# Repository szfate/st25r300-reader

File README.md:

# ST25R300-reader — NFC Reader Board

A compact, high-power NFC reader module built around the STMicroelectronics ST25R300 series. Packed into a 40x40mm board, it drives an onboard 4-turn center-tapped PCB antenna at up to 2.2 W, giving 4+ cm read range across a wide variety of tag form factors — including hard-to-read rings.

## Features

- NFC-A/B (ISO14443A/B), NFC-F (FeliCa), NFC-V (ISO15693, up to 212 kbps) support
- NFC initiator, target, reader, and card emulation modes; EMVCo PCD 3.2a compliant analog/digital
- Low-power card detection (LPCD) via I/Q antenna signal measurement
- Up to 2.2 W RF output power (extended range capable)
- 4+ cm read range across various tag form factors, including rings
- Dual supply: 5 V antenna/RF rail, separate IO supply
- Compact 40x40mm board

## The ST25R300 Chip

The ST25R300 is STMicroelectronics' high-performance NFC universal reader/transceiver IC. It supports NFC-A/B (ISO14443A/B), NFC-F (FeliCa), and NFC-V (ISO15693) protocols, and can operate as an NFC initiator, target, reader, or card emulator. It is designed to be compliant with the EMVCo PCD 3.2a analog and digital standards, making it suitable for contactless payment reader designs as well as general NFC/RFID applications.

- Manufacturer: STMicroelectronics
- Part: ST25R300-AQET
- Package: 32-pin UFQFPN-EP
- Datasheet/product page: https://www.st.com/en/nfc/st25r300.html
- Host interface: SPI
- Operating frequency: 13.56 MHz carrier (max 27.12 MHz internal)
- Supply range: wide supply voltage range 2.7 to 6.0 V (VDD); wide peripheral communication supply range 1.65 to 5.5 V (IO)
- Operating temperature: -40°C to +105°C
- RF output power: up to 2.2 W (extended range)
- Key features: low-power card detection (LPCD) using I/Q antenna signal measurement; NFC-A/NFC-F card emulation

## Board Specifications

| Spec | Value |
|---|---|
| Supply voltage | Dual rail: VTX 5 V antenna/RF supply; VIO host-provided IO supply (1.65–5.5 V) |
| Read range | 4+ cm, tested across various tag form factors including rings |
| Antenna tuning | Tuned to 15 Ω |
| Current consumption | ~0.25 A @ 5V|
| Operating temperature | -40°C to +105°C (chip rating — confirm board components match) |
| Dimensions | 40 x 40 mm |
| Antenna | Onboard PCB trace antenna, 4 turns, center-tapped |
| Host interface | SPI |

## Pinout

Connector: Molex PicoBlade 53261-0971, 1x9, 1.25mm pitch (`Conn_01x09`)

| Pin | Signal | Type | Description |
|---|---|---|---|
| 1 | CS | Input | SPI chip select (active low) |
| 2 | MOSI | Input | SPI master out / slave in |
| 3 | SCLK | Input | SPI clock |
| 4 | MISO | Output | SPI master in / slave out |
| 5 | RST | Input | Reset (optional — pulled down on-board; drive high to release reset) |
| 6 | IRQ | Output | Interrupt output |
| 7 | VTX | Power | Antenna/RF supply (5 V) |
| 8 | VIO | Power | IO supply (host-provided, 1.65–5.5 V) |
| 9 | GND | Power | Ground |

Signal directions in the table above are from the module's perspective: host → board for inputs, board → host for outputs.

## Connector

On-board connector: Molex PicoBlade, 1.25mm pitch, 1x9 position (53261-0971).

## Mechanical

| Spec | Value |
|---|---|
| Board dimensions | 40 x 40 mm |
| Mounting holes | 4x M3 (3.2 mm drill) on a 25 x 25 mm grid |
| Board thickness | 1.2 mm |
| Layer count | 4 |

Any metal near the antenna will detune the frequency and reduce read range/performance. Keep the antenna area clear of screws, connectors, enclosures, and other conductive objects. Use nylon screws for mounting to avoid affecting the antenna.

## How to Use

Firmware and host driver code are not provided with this board. To get started integrating the ST25R300, refer to the following repositories:

- [JohnMcLear/esphome_st25r](https://github.com/JohnMcLear/esphome_st25r) — ESPHome component for the ST25R300 NFC reader

## Certifications and Compliance

This board is **not certified** for regulatory or payment-scheme compliance. It is intended for **evaluation, development, and prototyping only**. While the ST25R300 IC is EMVCo PCD 3.2a analog/digital compliant, the assembled board has not undergone EMVCo, FCC, CE, or other required certifications. Do not use it in a production or end-user product without completing the appropriate testing and certification for your jurisdiction and application.

## Warnings

> **Hot!** The damping resistors connecting the antenna trace to the NFC reader reach approximately 80°C during operation. Over time this heats up the surrounding board area as well. Be cautious when touching the board during or shortly after use.

## Known Issues / Next Revision (R3) TODO

Nothing yet...

## License

Hardware design files in this repository are licensed under the **CERN Open Hardware Licence Version 2 - Weakly Reciprocal (CERN-OHL-W-2.0)**.

See [LICENSE](LICENSE) for the full license text.

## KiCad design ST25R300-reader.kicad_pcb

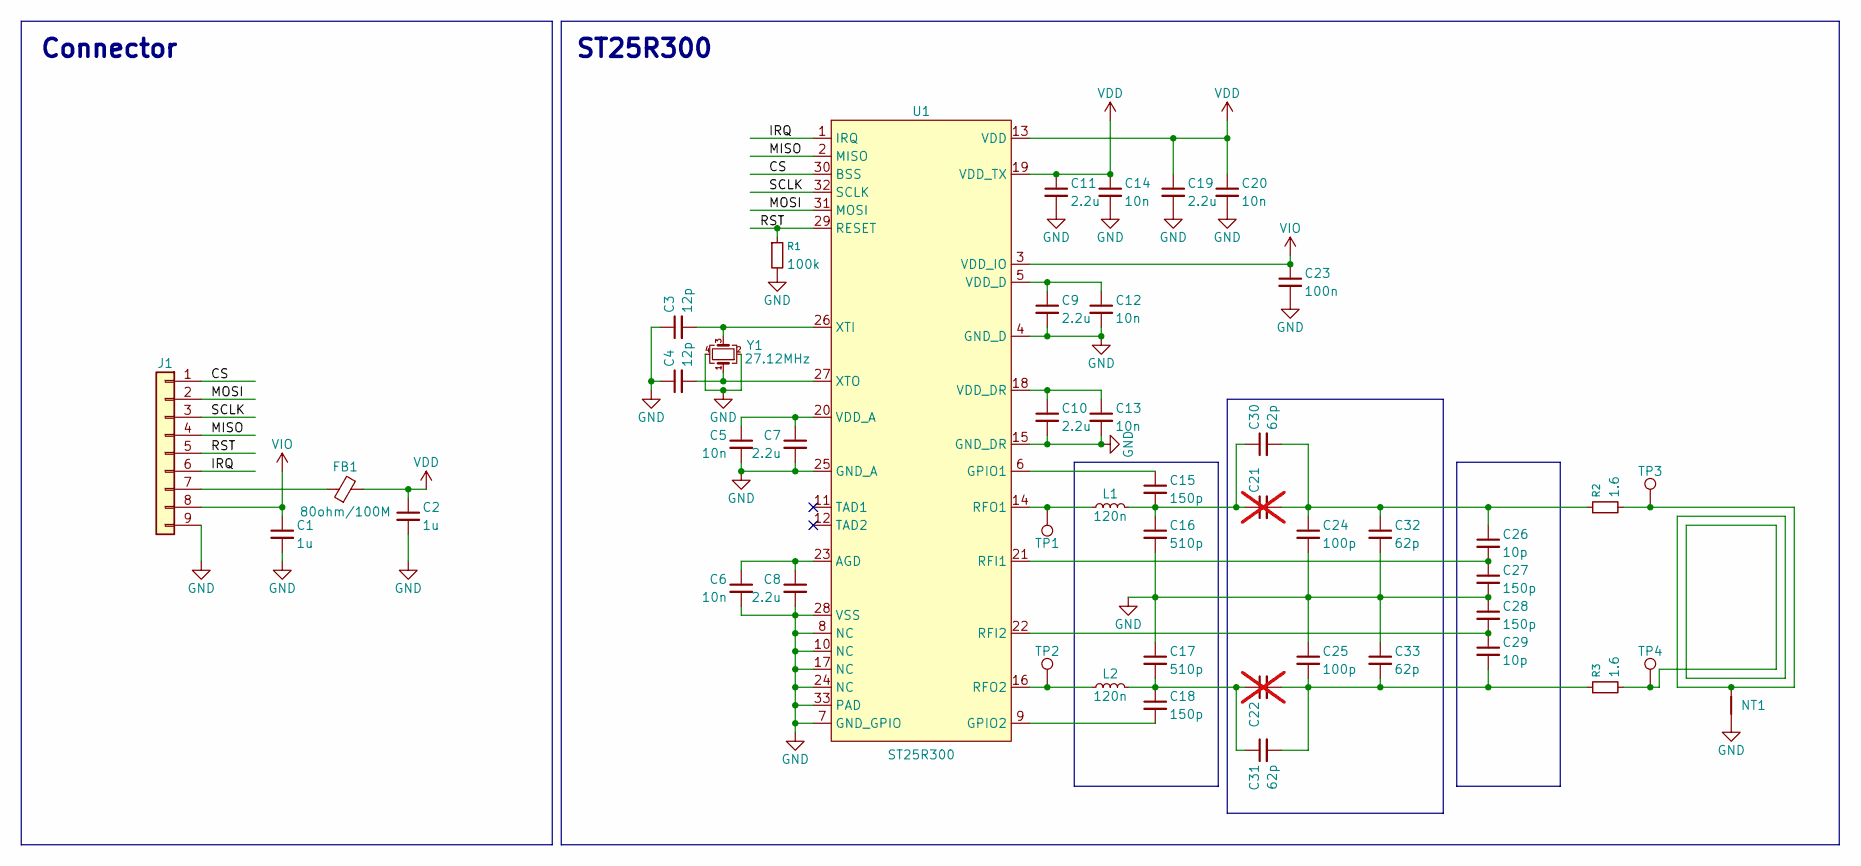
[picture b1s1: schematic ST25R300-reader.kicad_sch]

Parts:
C1, C2: 1u; C_0402_1005Metric; Part Number CL05A105KA5NQNC
C3, C4: 12p; C_0201_0603Metric; Part Number 0201CG120J500NT
C5, C6, C12, C13, C14, C20: 10n; C_0201_0603Metric; Part Number GRM033R71E103KE14D
C7, C8, C9, C10, C11, C19: 2.2u; C_0201_0603Metric; Part Number CL03A225MP3CRNC
C15, C18, C27, C28: 150p; C_0201_0603Metric; Part Number GRM0335C1H151JA01D
C16, C17: 510p; C_0402_1005Metric; Part Number GCM1555C1H511JA16D
C21, C22: C_0402_1005Metric; not fitted
C23: 100n; C_0201_0603Metric; Part Number GRM033R6YA104KE14D
C24, C25: 100p; C_0402_1005Metric; Part Number GCM1555C1H101FA16D
C26, C29: 10p; C_0201_0603Metric; Part Number GRM0335C1H100JA01D
C30, C31, C32, C33: 62p; C_0402_1005Metric; Part Number GRM1555C1H620GA01D
FB1: 80ohm/100M; L_0603_1608Metric; Part Number CBM160808U800T
J1: Conn_01x09; Molex_PicoBlade_53261-0971_1x09-1MP_P1.25mm_Horizontal; Part Number 532610971
L1, L2: 120n; L_0603_1608Metric; Part Number LQW18CNR12J0ZD
NT1: NetTie_2; NetTie-2_SMD_Pad0.5mm
R1: 100k; R_0201_0603Metric; Part Number RC0201FR-07100KL
R2, R3: 1.6; R_0603_1608Metric; Part Number RC0603JR-071R6L
TP1, TP2, TP3, TP4: TestPoint; Testpad-SMD-0.75mm
U1: ST25R300; UFQFPN-32-1EP_5x5mm_P0.5mm_EP3.5x3.5mm; Part Number ST25R300-AQET
Y1: 27.12MHz; Crystal_SMD_2016-4Pin_2.0x1.6mm; Part Number NX2016SA-27.12MHZ-EXS00A-CS06346

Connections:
/CS: J1.1, U1.30 (BSS)
/IRQ: J1.6, U1.1 (IRQ)
/MISO: J1.4, U1.2 (MISO)
/MOSI: J1.2, U1.31 (MOSI)
/RST: J1.5, R1.1, U1.29 (RESET)
/SCLK: J1.3, U1.32 (SCLK)
GND: C1.2, C2.2, C3.1, C4.1, C5.2, C6.2, C7.2, C8.2, C9.2, C10.2, C11.2, C12.2, C13.2, C14.2, C16.2, C17.1, C19.2, C20.2, C23.2, C24.2, C25.1, C27.2, C28.1, C32.2, C33.1, J1.9, NT1.1, R1.2, U1.4 (GND_D), U1.7 (GND_GPIO), U1.8 (NC), U1.10 (NC), U1.15 (GND_DR), U1.17 (NC), U1.24 (NC), U1.25 (GND_A), U1.28 (VSS), U1.33 (PAD), Y1.2, Y1.4
unnamed: C15.2, C16.1, C21.1, C30.1, L1.2
unnamed: C17.2, C18.1, C22.1, C31.1, L2.2
unnamed: C21.2, C24.1, C26.1, C30.2, C32.1, R2.1
unnamed: C22.2, C25.2, C29.2, C31.2, C33.2, R3.1
unnamed: FB1.1, J1.7
unnamed: NT1.2, R2.2, R3.2, TP3.1 (1_1), TP4.1 (1_1)
unnamed: C6.1, C8.1, U1.23 (AGD)
unnamed: C15.1, U1.6 (GPIO1)
unnamed: C18.2, U1.9 (GPIO2)
unnamed: C26.2, C27.1, U1.21 (RFI1)
unnamed: C28.2, C29.1, U1.22 (RFI2)
unnamed: L1.1, TP1.1 (1_1), U1.14 (RFO1)
unnamed: L2.1, TP2.1 (1_1), U1.16 (RFO2)
unnamed: C5.1, C7.1, U1.20 (VDD_A)
unnamed: C9.1, C12.1, U1.5 (VDD_D)
unnamed: C10.1, C13.1, U1.18 (VDD_DR)
unnamed: C3.2, U1.26 (XTI), Y1.3
unnamed: C4.2, U1.27 (XTO), Y1.1
VDD: C2.1, C11.1, C14.1, C19.1, C20.1, FB1.2, U1.13 (VDD), U1.19 (VDD_TX)
VIO: C1.1, C23.1, J1.8, U1.3 (VDD_IO)

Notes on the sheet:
ST25R300
Connector

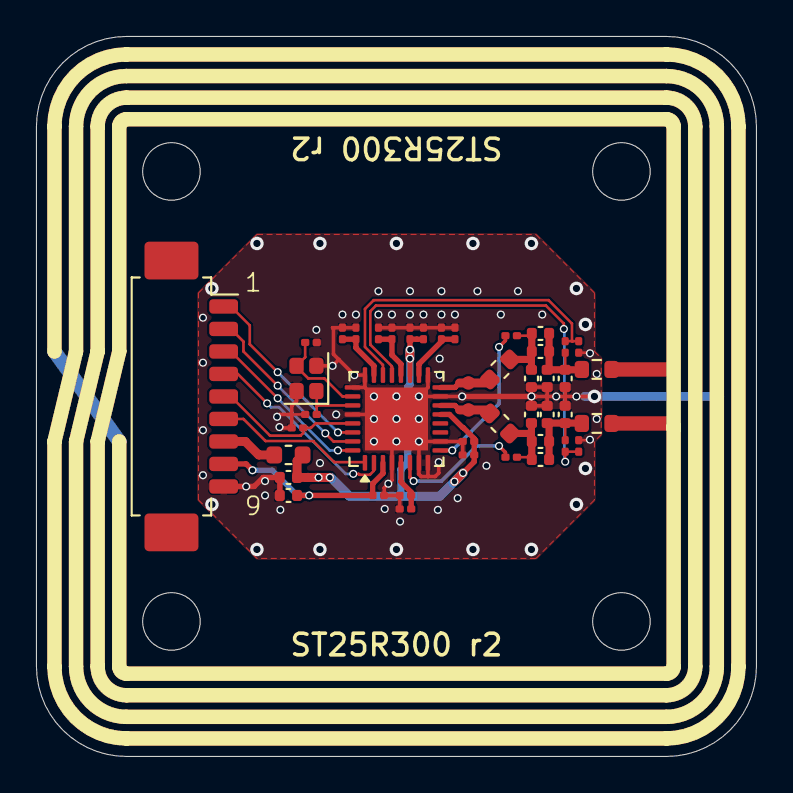
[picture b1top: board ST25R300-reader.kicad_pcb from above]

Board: 4 copper layers, 40.0 x 40.0 mm, 47 parts (1 on the bottom side), 27 nets.

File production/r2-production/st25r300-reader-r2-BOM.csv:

"Reference","Qty","Value","Part Number","Footprint","DNP","Datasheet"
"C1,C2","2","1u","CL05A105KA5NQNC","Capacitor_SMD:C_0402_1005Metric","",""
"C3,C4","2","12p","0201CG120J500NT","Capacitor_SMD:C_0201_0603Metric","",""
"C5,C6,C12,C13,C14,C20","6","10n","GRM033R71E103KE14D","Capacitor_SMD:C_0201_0603Metric","",""
"C7,C8,C9,C10,C11,C19","6","2.2u","CL03A225MP3CRNC","Capacitor_SMD:C_0201_0603Metric","",""
"C15,C18,C27,C28","4","150p","GRM0335C1H151JA01D","Capacitor_SMD:C_0201_0603Metric","",""
"C16,C17","2","510p","GCM1555C1H511JA16D","Capacitor_SMD:C_0402_1005Metric","",""
"C21,C22","2","","","Capacitor_SMD:C_0402_1005Metric","DNP",""
"C23","1","100n","GRM033R6YA104KE14D","Capacitor_SMD:C_0201_0603Metric","",""
"C24,C25","2","100p","GCM1555C1H101FA16D","Capacitor_SMD:C_0402_1005Metric","",""
"C26,C29","2","10p","GRM0335C1H100JA01D","Capacitor_SMD:C_0201_0603Metric","",""
"C30,C31,C32,C33","4","62p","GRM1555C1H620GA01D","Capacitor_SMD:C_0402_1005Metric","",""
"FB1","1","80ohm/100M","CBM160808U800T","Inductor_SMD:L_0603_1608Metric","",""
"J1","1","Conn_01x09","532610971","Connector_Molex:Molex_PicoBlade_53261-0971_1x09-1MP_P1.25mm_Horizontal","",""
"L1,L2","2","120n","LQW18CNR12J0ZD","Inductor_SMD:L_0603_1608Metric","",""
"R1","1","100k","RC0201FR-07100KL","Resistor_SMD:R_0201_0603Metric","",""
"R2,R3","2","1.6","RC0603JR-071R6L","Resistor_SMD:R_0603_1608Metric","",""
"U1","1","ST25R300","ST25R300-AQET","Package_DFN_QFN:UFQFPN-32-1EP_5x5mm_P0.5mm_EP3.5x3.5mm","",""
"Y1","1","27.12MHz","NX2016SA-27.12MHZ-EXS00A-CS06346","Crystal:Crystal_SMD_2016-4Pin_2.0x1.6mm","",""

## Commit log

2026-06-25 Initial commit. Updated PCB to r2.
